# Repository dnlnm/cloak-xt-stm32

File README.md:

# cloak-xt-stm32

PCB for Cloak XT

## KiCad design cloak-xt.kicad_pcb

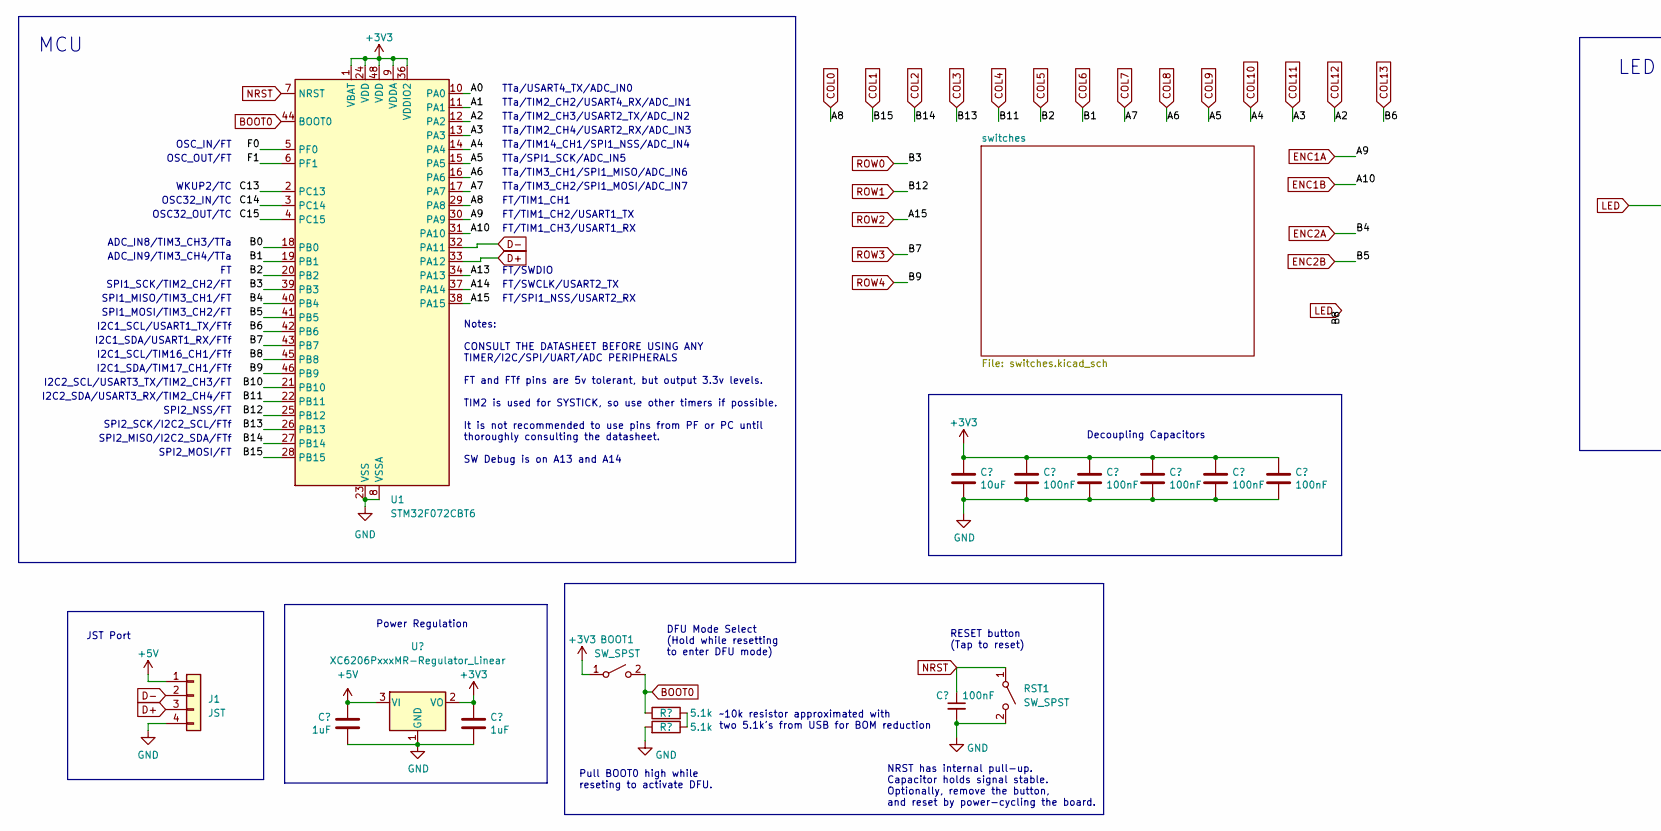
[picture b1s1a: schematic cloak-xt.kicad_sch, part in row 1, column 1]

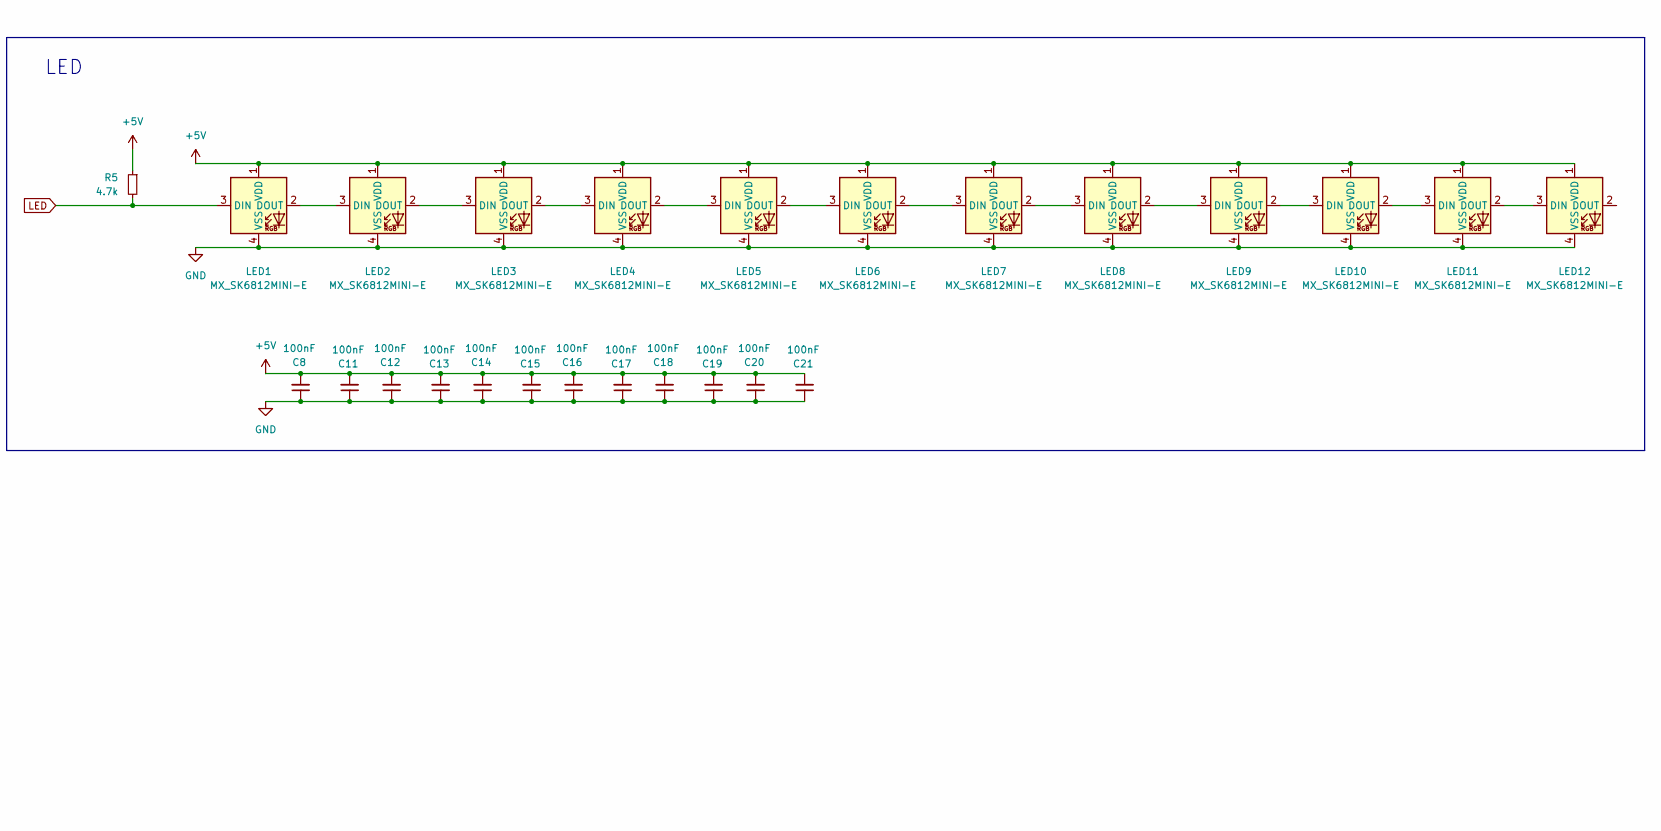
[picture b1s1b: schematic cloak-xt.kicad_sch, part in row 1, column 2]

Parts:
BOOT1: SW_SPST; SW_SPST_TL3342
C1, C3, C4, C5, C6, C7: 100nF; C_0402_1005Metric; LCSC C307331
C2: 10uF; C_0603_1608Metric; LCSC C307331
C8, C11, C12, C13, C14, C15, C16, C17, C18, C19, C20, C21: 100nF; C_0402_1005Metric
C9, C10: 1uF; C_0402_1005Metric; LCSC C307331
J1: JST; JST_SH_SM04B-SRSS-TB_1x04-1MP_P1.00mm_Horizontal
LED1, LED2, LED3, LED4, LED5, LED6, LED7, LED8, LED9, LED10: MX_SK6812MINI-E; LED_MX_6028R
LED11, LED12: MX_SK6812MINI-E; LED_6028R
R3, R4: 5.1k; R_0402_1005Metric
R5: 4.7k; R_0402_1005Metric
RST1: SW_SPST; SW_SPST_TL3342
U1: STM32F072CBT6; LQFP-48_7x7mm_P0.5mm; JlcRotOffset 90
U3: XC6206PxxxMR-Regulator_Linear; SOT-23; LCSC C5446

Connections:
+3V3: BOOT1.1 (A), C2.1, C3.1, C4.1, C5.1, C6.1, C7.1, C10.1, U1.1 (VBAT), U1.9 (VDDA), U1.24 (VDD), U1.36 (VDDIO2), U1.48 (VDD), U3.2 (VO); also elsewhere on the board
+5V: C8.2, C9.1, C11.2, C12.2, C13.2, C14.2, C15.2, C16.2, C17.2, C18.2, C19.2, C20.2, C21.2, J1.1, LED1.1 (VDD), LED2.1 (VDD), LED3.1 (VDD), LED4.1 (VDD), LED5.1 (VDD), LED6.1 (VDD), LED7.1 (VDD), LED8.1 (VDD), LED9.1 (VDD), LED10.1 (VDD), LED11.1 (VDD), LED12.1 (VDD), R5.1, U3.3 (VI)
/A0: U1.10 (PA0)
/A1: U1.11 (PA1)
/A13: U1.34 (PA13)
/A14: U1.37 (PA14)
/B0: U1.18 (PB0)
/B10: U1.21 (PB10)
/C13: U1.2 (PC13)
/C14: U1.3 (PC14)
/C15: U1.4 (PC15)
/F0: U1.5 (PF0)
/F1: U1.6 (PF1)
BOOT0: BOOT1.2 (B), R3.1, U1.44 (BOOT0)
COL0: U1.29 (PA8); also elsewhere on the board
COL1: U1.28 (PB15); also elsewhere on the board
COL2: U1.27 (PB14); also elsewhere on the board
COL3: U1.26 (PB13); also elsewhere on the board
COL4: U1.22 (PB11); also elsewhere on the board
COL5: U1.20 (PB2); also elsewhere on the board
COL6: U1.19 (PB1); also elsewhere on the board
COL7: U1.17 (PA7); also elsewhere on the board
COL8: U1.16 (PA6); also elsewhere on the board
COL9: U1.15 (PA5); also elsewhere on the board
COL10: U1.14 (PA4); also elsewhere on the board
COL11: U1.13 (PA3); also elsewhere on the board
COL12: U1.12 (PA2); also elsewhere on the board
COL13: U1.42 (PB6); also elsewhere on the board
D+: J1.3, U1.33 (PA12)
D-: J1.2, U1.32 (PA11)
ENC1A: U1.30 (PA9); also elsewhere on the board
ENC1B: U1.31 (PA10); also elsewhere on the board
ENC2A: U1.40 (PB4); also elsewhere on the board
ENC2B: U1.41 (PB5); also elsewhere on the board
GND: C1.2, C2.2, C3.2, C4.2, C5.2, C6.2, C7.2, C8.1, C9.2, C10.2, C11.1, C12.1, C13.1, C14.1, C15.1, C16.1, C17.1, C18.1, C19.1, C20.1, C21.1, J1.4, LED1.4 (VSS), LED2.4 (VSS), LED3.4 (VSS), LED4.4 (VSS), LED5.4 (VSS), LED6.4 (VSS), LED7.4 (VSS), LED8.4 (VSS), LED9.4 (VSS), LED10.4 (VSS), LED11.4 (VSS), LED12.4 (VSS), R4.2, RST1.2 (B), U1.8 (VSSA), U1.23 (VSS), U1.35 (VSS), U1.47 (VSS), U3.1 (GND); also elsewhere on the board
LED: LED1.3 (DIN), R5.2, U1.45 (PB8)
NRST: C1.1, RST1.1 (A), U1.7 (NRST)
unnamed: LED1.2 (DOUT), LED2.3 (DIN)
unnamed: LED2.2 (DOUT), LED3.3 (DIN)
unnamed: LED3.2 (DOUT), LED4.3 (DIN)
unnamed: LED4.2 (DOUT), LED5.3 (DIN)
unnamed: LED5.2 (DOUT), LED6.3 (DIN)
unnamed: LED6.2 (DOUT), LED7.3 (DIN)
unnamed: LED7.2 (DOUT), LED8.3 (DIN)
unnamed: LED8.2 (DOUT), LED9.3 (DIN)
unnamed: LED9.2 (DOUT), LED10.3 (DIN)
unnamed: LED10.2 (DOUT), LED11.3 (DIN)
unnamed: LED11.2 (DOUT), LED12.3 (DIN)
unnamed: R3.2, R4.1
ROW0: U1.39 (PB3); also elsewhere on the board
ROW1: U1.25 (PB12); also elsewhere on the board
ROW2: U1.38 (PA15); also elsewhere on the board
ROW3: U1.43 (PB7); also elsewhere on the board
ROW4: U1.46 (PB9); also elsewhere on the board

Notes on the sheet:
SPI1_SCK/TIM2_CH2/FT
FT/TIM1_CH1
FT/TIM1_CH3/USART1_RX
SPI2_NSS/FT
Notes: CONSULT THE DATASHEET BEFORE USING ANY TIMER/I2C/SPI/UART/ADC PERIPHERALS FT and FTf pins are 5v tolerant, but output 3.3v levels. TIM2 is used for SYSTICK, so use other timers if possible. It is not recommended to use pins from PF or PC until thoroughly consulting the datasheet. SW Debug is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
TTa/TIM2_CH4/USART2_RX/ADC_IN3
NRST has internal pull-up. Capacitor holds signal stable. Optionally, remove the button, and reset by power-cycling the board.
FT/SWDIO
Decoupling Capacitors
SPI1_MOSI/TIM3_CH2/FT
ADC_IN9/TIM3_CH4/TTa
I2C2_SCL/USART3_TX/TIM2_CH3/FT
MCU
SPI2_MISO/I2C2_SDA/FTf
FT/SWCLK/USART2_TX
I2C1_SCL/TIM16_CH1/FTf
~10k resistor approximated with two 5.1k's from USB for BOM reduction
TTa/TIM2_CH2/USART4_RX/ADC_IN1
JST Port
TTa/TIM2_CH3/USART2_TX/ADC_IN2
OSC_IN/FT
DFU Mode Select (Hold while resetting to enter DFU mode)
WKUP2/TC
I2C2_SDA/USART3_RX/TIM2_CH4/FT
ADC_IN8/TIM3_CH3/TTa
RESET button (Tap to reset)
Pull BOOT0 high while reseting to activate DFU.
I2C1_SDA/TIM17_CH1/FTf
TTa/SPI1_SCK/ADC_IN5
TTa/TIM3_CH1/SPI1_MISO/ADC_IN6
TTa/TIM3_CH2/SPI1_MOSI/ADC_IN7
OSC32_OUT/TC
FT/SPI1_NSS/USART2_RX
SPI1_MISO/TIM3_CH1/FT
OSC32_IN/TC
LED
TTa/TIM14_CH1/SPI1_NSS/ADC_IN4
I2C1_SDA/USART1_RX/FTf
SPI2_MOSI/FT
FT/TIM1_CH2/USART1_TX

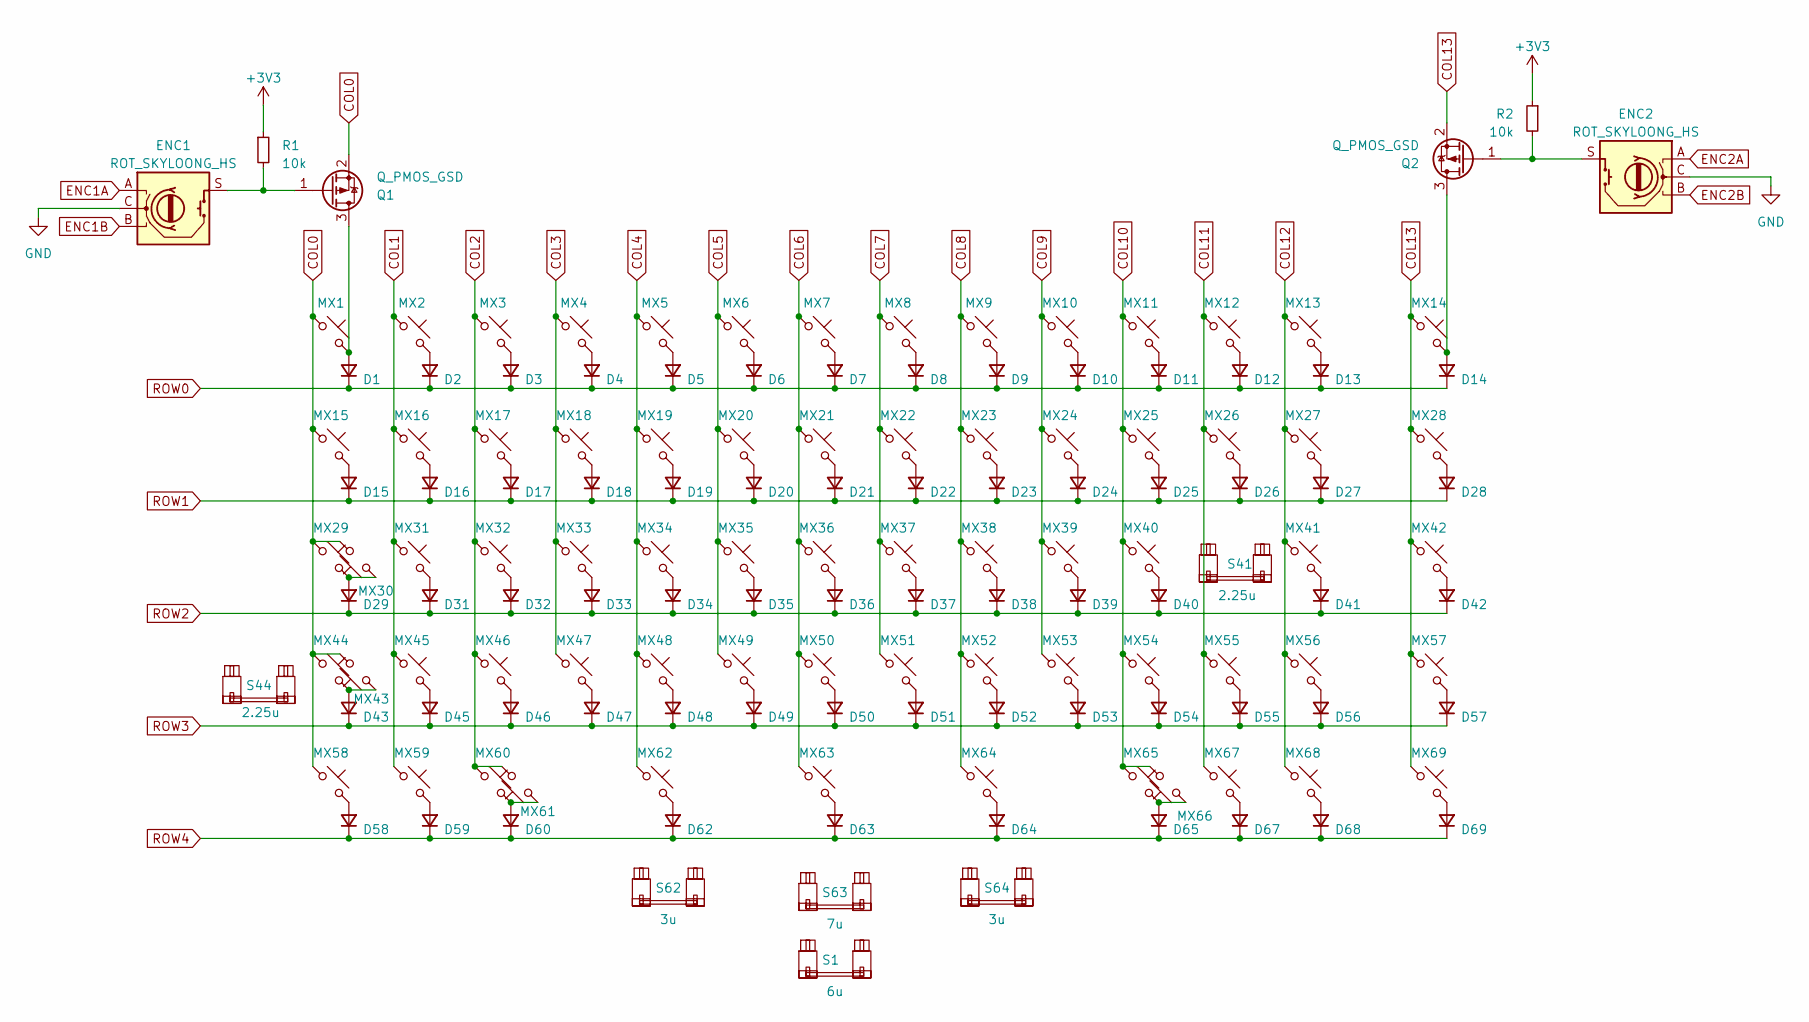
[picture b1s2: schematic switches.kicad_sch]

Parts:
D1, D2, D3, D4, D5, D6, D7, D8, D9, D10, D11, D12, D13, D14, D15, D16, D17, D18, D19, D20, D21, D22, D23, D24, D25, D26, D27, D28, D29, D31, D32, D33, D34, D35, D36, D37, D38, D39, D40, D41, D42, D43, D45, D46, D47, D48, D49, D50, D51, D52, D53, D54, D55, D56, D57, D58, D59, D60, D62, D63, D64, D65, D67, D68, D69: D_Small; D_SOD-123
ENC1, ENC2: ROT_SKYLOONG_HS; ROT_SKYLOONG_HS-Switch
MX1, MX2, MX3, MX4, MX5, MX6, MX7, MX8, MX9, MX10, MX11, MX12, MX13, MX14, MX16, MX17, MX18, MX19, MX20, MX21, MX22, MX23, MX24, MX25, MX27, MX28, MX31, MX32, MX33, MX34, MX35, MX36, MX37, MX38, MX39, MX40, MX41, MX42, MX44, MX45, MX46, MX47, MX48, MX49, MX50, MX51, MX52, MX53, MX54, MX55, MX57, MX59, MX60, MX62, MX63, MX64, MX65, MX67, MX69: MX_SW_HS; SW_MX_HS_CPG151101S11_1u
MX15, MX26, MX58, MX61, MX66, MX68: MX_SW_HS; SW_MX_HS_CPG151101S11_1.5u
MX29: MX_SW_HS; SW_MX_HS_CPG151101S11_1.75u_STP_1.25
MX30, MX56: MX_SW_HS; SW_MX_HS_CPG151101S11_1.75u
MX43: MX_SW_HS; SW_MX_HS_CPG151101S11_1.25u
Q1, Q2: Q_PMOS_GSD; SOT-23
R1, R2: 10k; R_0603_1608Metric
S1: 6u; STAB_MX_P_6u
S41, S44: 2.25u; STAB_MX_P_2.25u
S62, S64: 3u; STAB_MX_P_3u
S63: 7u; STAB_MX_P_7u

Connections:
+3V3: R1.1, R2.1; also elsewhere on the board
COL0: MX1.1, MX15.1, MX29.1, MX30.2, MX43.2, MX44.1, MX58.1, Q1.2 (S); also elsewhere on the board
COL1: MX2.1, MX16.1, MX31.1, MX45.1, MX59.1; also elsewhere on the board
COL2: MX3.1, MX17.1, MX32.1, MX46.1, MX60.1, MX61.2; also elsewhere on the board
COL3: MX4.1, MX18.1, MX33.1, MX47.1; also elsewhere on the board
COL4: MX5.1, MX19.1, MX34.1, MX48.1, MX62.1; also elsewhere on the board
COL5: MX6.1, MX20.1, MX35.1, MX49.1; also elsewhere on the board
COL6: MX7.1, MX21.1, MX36.1, MX50.1, MX63.1; also elsewhere on the board
COL7: MX8.1, MX22.1, MX37.1, MX51.1; also elsewhere on the board
COL8: MX9.1, MX23.1, MX38.1, MX52.1, MX64.1; also elsewhere on the board
COL9: MX10.1, MX24.1, MX39.1, MX53.1; also elsewhere on the board
COL10: MX11.1, MX25.1, MX40.1, MX54.1, MX65.1, MX66.2; also elsewhere on the board
COL11: MX12.1, MX26.1, MX55.1, MX67.1; also elsewhere on the board
COL12: MX13.1, MX27.1, MX41.1, MX56.1, MX68.1; also elsewhere on the board
COL13: MX14.1, MX28.1, MX42.1, MX57.1, MX69.1, Q2.2 (S); also elsewhere on the board
ENC1A: ENC1.A; also elsewhere on the board
ENC1B: ENC1.B; also elsewhere on the board
ENC2A: ENC2.A; also elsewhere on the board
ENC2B: ENC2.B; also elsewhere on the board
GND: ENC1.C, ENC2.C; also elsewhere on the board
unnamed: D1.2 (A), MX1.2, Q1.3 (D)
unnamed: D2.2 (A), MX2.2
unnamed: D3.2 (A), MX3.2
unnamed: D4.2 (A), MX4.2
unnamed: D5.2 (A), MX5.2
unnamed: D6.2 (A), MX6.2
unnamed: D7.2 (A), MX7.2
unnamed: D8.2 (A), MX8.2
unnamed: D9.2 (A), MX9.2
unnamed: D10.2 (A), MX10.2
unnamed: D11.2 (A), MX11.2
unnamed: D12.2 (A), MX12.2
unnamed: D13.2 (A), MX13.2
unnamed: D14.2 (A), MX14.2, Q2.3 (D)
unnamed: D15.2 (A), MX15.2
unnamed: D16.2 (A), MX16.2
unnamed: D17.2 (A), MX17.2
unnamed: D18.2 (A), MX18.2
unnamed: D19.2 (A), MX19.2
unnamed: D20.2 (A), MX20.2
unnamed: D21.2 (A), MX21.2
unnamed: D22.2 (A), MX22.2
unnamed: D23.2 (A), MX23.2
unnamed: D24.2 (A), MX24.2
unnamed: D25.2 (A), MX25.2
unnamed: D26.2 (A), MX26.2
unnamed: D27.2 (A), MX27.2
unnamed: D28.2 (A), MX28.2
unnamed: D29.2 (A), MX29.2, MX30.1
unnamed: D31.2 (A), MX31.2
unnamed: D32.2 (A), MX32.2
unnamed: D33.2 (A), MX33.2
unnamed: D34.2 (A), MX34.2
unnamed: D35.2 (A), MX35.2
unnamed: D36.2 (A), MX36.2
unnamed: D37.2 (A), MX37.2
unnamed: D38.2 (A), MX38.2
unnamed: D39.2 (A), MX39.2
unnamed: D40.2 (A), MX40.2
unnamed: D41.2 (A), MX41.2
unnamed: D42.2 (A), MX42.2
unnamed: D43.2 (A), MX43.1, MX44.2
unnamed: D45.2 (A), MX45.2
unnamed: D46.2 (A), MX46.2
unnamed: D47.2 (A), MX47.2
unnamed: D48.2 (A), MX48.2
unnamed: D49.2 (A), MX49.2
unnamed: D50.2 (A), MX50.2
unnamed: D51.2 (A), MX51.2
unnamed: D52.2 (A), MX52.2
unnamed: D53.2 (A), MX53.2
unnamed: D54.2 (A), MX54.2
unnamed: D55.2 (A), MX55.2
unnamed: D56.2 (A), MX56.2
unnamed: D57.2 (A), MX57.2
unnamed: D58.2 (A), MX58.2
unnamed: D59.2 (A), MX59.2
unnamed: D60.2 (A), MX60.2, MX61.1
unnamed: D62.2 (A), MX62.2
unnamed: D63.2 (A), MX63.2
unnamed: D64.2 (A), MX64.2
unnamed: D65.2 (A), MX65.2, MX66.1
unnamed: D67.2 (A), MX67.2
unnamed: D68.2 (A), MX68.2
unnamed: D69.2 (A), MX69.2
unnamed: ENC1.S, Q1.1 (G), R1.2
unnamed: ENC2.S, Q2.1 (G), R2.2
ROW0: D1.1 (K), D2.1 (K), D3.1 (K), D4.1 (K), D5.1 (K), D6.1 (K), D7.1 (K), D8.1 (K), D9.1 (K), D10.1 (K), D11.1 (K), D12.1 (K), D13.1 (K), D14.1 (K); also elsewhere on the board
ROW1: D15.1 (K), D16.1 (K), D17.1 (K), D18.1 (K), D19.1 (K), D20.1 (K), D21.1 (K), D22.1 (K), D23.1 (K), D24.1 (K), D25.1 (K), D26.1 (K), D27.1 (K), D28.1 (K); also elsewhere on the board
ROW2: D29.1 (K), D31.1 (K), D32.1 (K), D33.1 (K), D34.1 (K), D35.1 (K), D36.1 (K), D37.1 (K), D38.1 (K), D39.1 (K), D40.1 (K), D41.1 (K), D42.1 (K); also elsewhere on the board
ROW3: D43.1 (K), D45.1 (K), D46.1 (K), D47.1 (K), D48.1 (K), D49.1 (K), D50.1 (K), D51.1 (K), D52.1 (K), D53.1 (K), D54.1 (K), D55.1 (K), D56.1 (K), D57.1 (K); also elsewhere on the board
ROW4: D58.1 (K), D59.1 (K), D60.1 (K), D62.1 (K), D63.1 (K), D64.1 (K), D65.1 (K), D67.1 (K), D68.1 (K), D69.1 (K); also elsewhere on the board

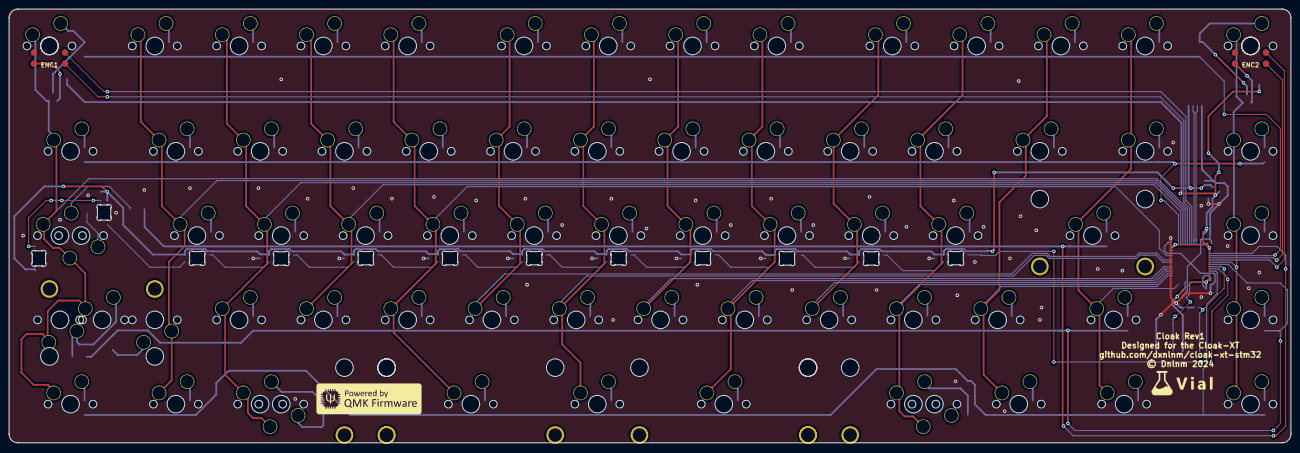
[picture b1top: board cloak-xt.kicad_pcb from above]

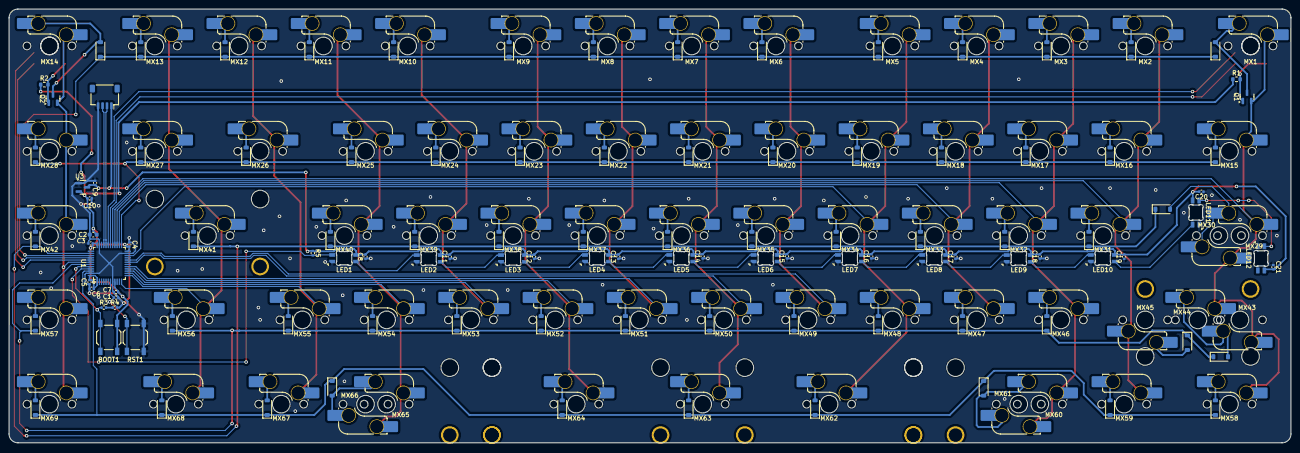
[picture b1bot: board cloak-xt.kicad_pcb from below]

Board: 2 copper layers, 289.7 x 98.0 mm, 187 parts (179 on the bottom side), 110 nets.

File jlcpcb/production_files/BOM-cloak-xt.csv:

Comment,Designator,Footprint,LCSC
Q_PMOS_GSD,"Q1,Q2",SOT-23,C15127
100nF,"C11,C12,C13,C14,C15,C16,C17,C18,C19,C20,C21,C8",C_0402_1005Metric,C1525
10k,"R1,R2",R_0603_1608Metric,C25804
4.7k,R5,R_0402_1005Metric,C25900
5.1k,"R3,R4",R_0402_1005Metric,C25905
JST,J1,JST_SH_SM04B-SRSS-TB_1x04-1MP_P1.00mm_Horizontal,C3029343
100nF,"C1,C10,C2,C3,C4,C5,C6,C7,C9",C_0402_1005Metric,C307331
SW_SPST,"BOOT1,RST1",SW_SPST_TL3342,C318884
MX_SK6812MINI-E,"LED1,LED10,LED11,LED12,LED2,LED3,LED4,LED5,LED6,LED7,LED8,LED9",LED_MX_6028R-ROT,C5149201
XC6206PxxxMR-Regulator_Linear,U3,SOT-23,C5446
D_Small,"D1,D10,D11,D12,D13,D14,D15,D16,D17,D18,D19,D2,D20,D21,D22,D23,D24,D25,D26,D27,D28,D29,D3,D31,D32,D33,D34,D35,D36,D37,D38,D39,D4,D40,D41,D42,D43,D45,D46,D47,D48,D49,D5,D50,D51,D52,D53,D54,D55,D56,D57,D58,D59,D6,D60,D62,D63,D64,D65,D67,D68,D69,D7,D8,D9",D_SOD-123,C81598
STM32F072CBT6,U1,LQFP-48_7x7mm_P0.5mm,C81720

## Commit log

2024-08-13 Create KiCad Project
2024-08-13 Update STM32 from template
2024-08-13 Remove pin headers and edge cuts
2024-08-13 Init matrix
2024-08-13 Update PCB from schematics
2024-08-13 Fixed diodes notation
2024-08-13 Add edge cuts
2024-08-13 Remove onboard USB/ESD and add JST
2024-08-13 Update JST on PCB
2024-08-13 Complete matrix and add Skyloong knob module
2024-08-14 Complete column traces
2024-08-14 Complete initial colum,n/row traces
2024-08-16 Change switches text placement
2024-08-16 Complete BOOT/RST traces
2024-08-16 Complete initial PCB
    Complete PCB traces with matrix and ground planes. No GND vias yet.
2024-08-17 Add schematics for SK6812MINI-E on Capslock/Stepped
2024-08-17 Add schematics for RGB lighting
2024-08-17 Initiate files for JLCPCB
2024-08-18 Complete SK6812 LED traces
2024-08-19 Retrace 5V for SK6812
2024-08-19 Fixed and ignore silkscreen clipping
2024-08-19 Fix PF/PC pins and change LED pin to B8
2024-08-20 Fix GND and add vias
2024-08-23 Prepare traces for rounded tracks
2024-08-23 Add logo footprints
2024-08-25 Add line artwork
2024-08-25 Change MX text under switches
2024-08-25 Remove/Hide unwanted text on B.Silkscreen
2024-08-26 Swap LED pin with ENC2B for TIM3_CH2
2024-08-26 Add pin for SW Debug
2024-08-26 Add pins breakout
2024-08-27 Reroute some columns trace
2024-08-28 Add spacebar 6.25u/2.25u/2.75u and remove 6u/3u/3u
2024-08-29 Swap Backspace and DEL keys

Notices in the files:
cloak-xt.kicad_pcb:
©️ Dnlnm 2024
